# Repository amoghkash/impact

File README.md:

# impact
 impact concussion detection

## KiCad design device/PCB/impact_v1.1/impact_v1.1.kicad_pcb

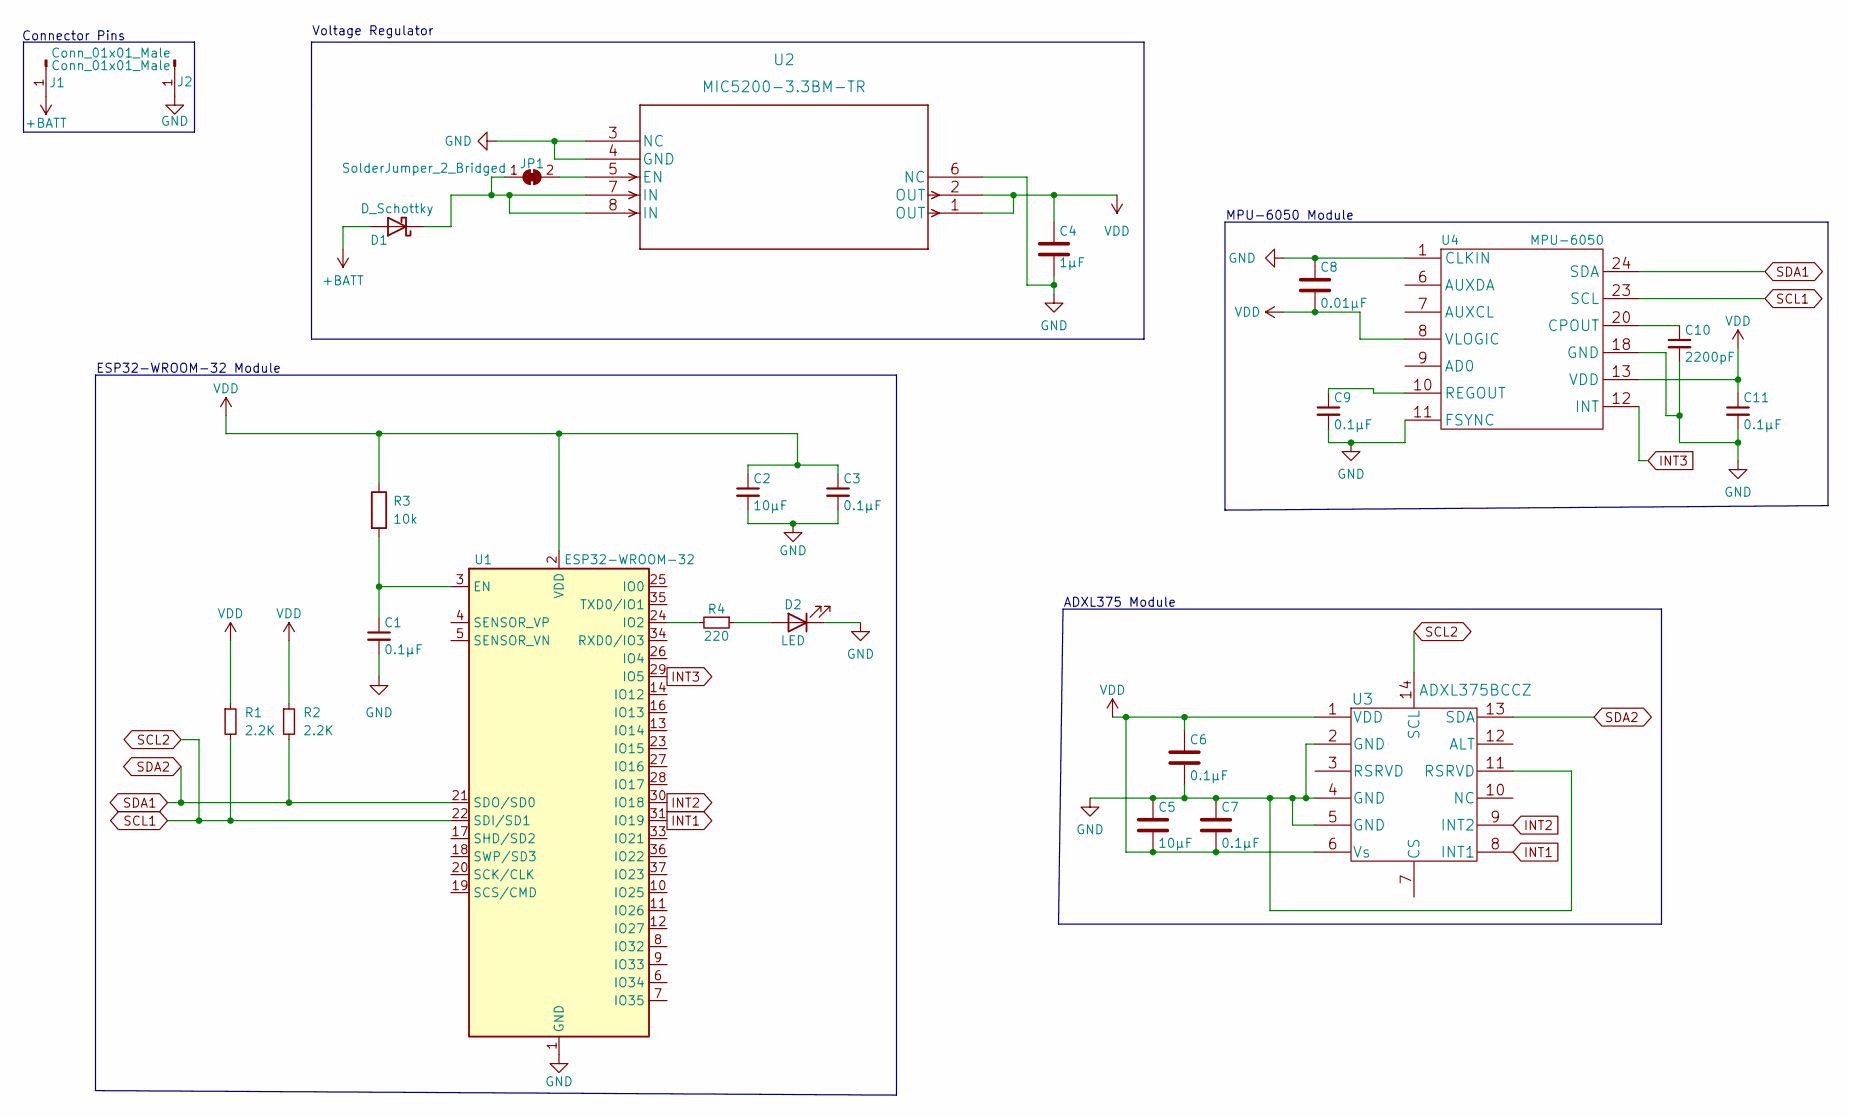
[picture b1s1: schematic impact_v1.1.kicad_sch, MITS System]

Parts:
C1, C3, C6, C7, C9, C11: 0.1µF; C_0201_0603Metric_Pad0.64x0.40mm_HandSolder
C2, C5: 10µF; C_0603_1608Metric_Pad1.08x0.95mm_HandSolder
C4: 1µF; C_0402_1005Metric_Pad0.74x0.62mm_HandSolder
C8: 0.01µF; C_0201_0603Metric_Pad0.64x0.40mm_HandSolder
C10: 2200pF; C_0402_1005Metric_Pad0.74x0.62mm_HandSolder
D1: D_Schottky; D_0402_1005Metric_Pad0.77x0.64mm_HandSolder
D2: LED; LED_0402_1005Metric_Pad0.77x0.64mm_HandSolder
J1: Conn_01x01_Male; TestPoint_Pad_3.0x3.0mm
J2: Conn_01x01_Male; TestPoint_Pad_D3.0mm
JP1: SolderJumper_2_Bridged; SolderJumper-2_P1.3mm_Bridged_Pad1.0x1.5mm
R1, R2: 2.2K; R_0201_0603Metric_Pad0.64x0.40mm_HandSolder
R3: 10k; R_0201_0603Metric_Pad0.64x0.40mm_HandSolder
R4: 220; R_0201_0603Metric_Pad0.64x0.40mm_HandSolder
U1: ESP32-WROOM-32
U2: MIC5200-3.3BM-TR; MIC5200-3.3YM
U3: ADXL375BCCZ
U4: MPU-6050; InvenSense_QFN-24_4x4mm_P0.5mm

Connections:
+BATT: D1.2 (A), J1.1; also elsewhere on the board
GND: C1.2, C2.2, C3.2, C4.2, C5.1, C6.2, C7.1, C8.1, C9.2, C10.2, C11.2, D2.1 (K), J2.1, U1.1 (GND), U1.15 (GND), U1.38 (GND), U1.39 (GND), U2.3 (NC), U2.4 (GND), U2.6 (NC), U3.2 (GND), U3.4 (GND), U3.5 (GND), U3.11 (RSRVD), U4.1 (CLKIN), U4.11 (FSYNC), U4.18 (GND); also elsewhere on the board
INT1: U1.31 (IO19), U3.8 (INT1)
INT2: U1.30 (IO18), U3.9 (INT2)
INT3: U1.29 (IO5), U4.12 (INT)
unnamed: C1.1, R3.2, U1.3 (EN)
unnamed: C9.1, U4.10 (REGOUT)
unnamed: C10.1, U4.20 (CPOUT)
unnamed: D1.1 (K), JP1.1 (A), U2.7 (IN), U2.8 (IN)
unnamed: D2.2 (A), R4.1
unnamed: JP1.2 (B), U2.5 (EN)
unnamed: R4.2, U1.24 (IO2)
SCL1: R1.2, U1.22 (SDI/SD1), U3.14 (SCL), U4.23 (SCL)
SDA1: R2.2, U1.21 (SDO/SD0), U3.13 (SDA), U4.24 (SDA)
VDD: C2.1, C3.1, C4.1, C5.2, C6.1, C7.2, C8.2, C11.1, R1.1, R2.1, R3.1, U1.2 (VDD), U2.1 (OUT), U2.2 (OUT), U3.1 (VDD), U3.6 (Vs), U4.8 (VLOGIC), U4.13 (VDD)

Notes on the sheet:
MPU-6050 Module
Connector Pins
ESP32-WROOM-32 Module
Voltage Regulator
ADXL375 Module

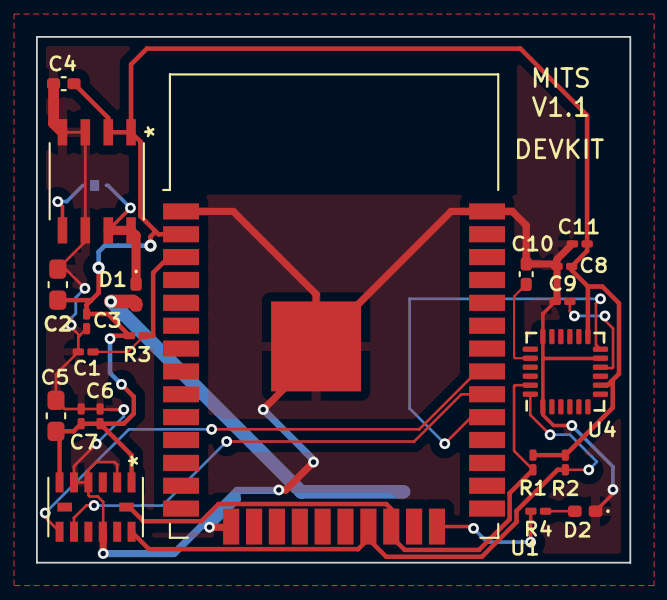
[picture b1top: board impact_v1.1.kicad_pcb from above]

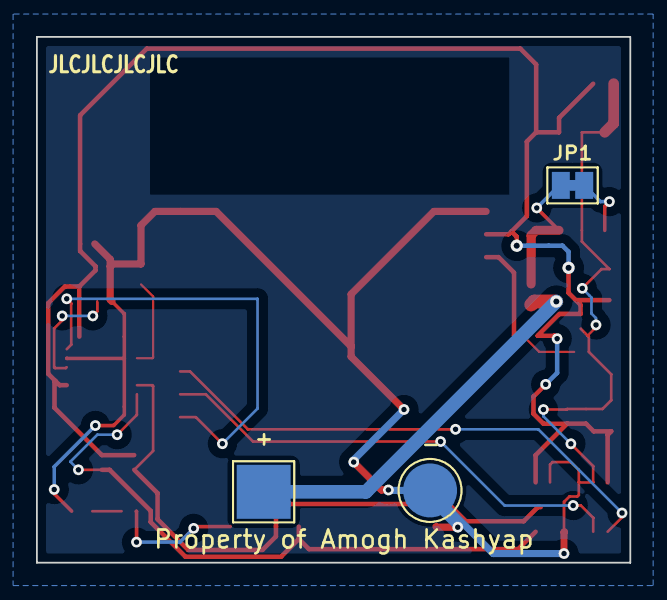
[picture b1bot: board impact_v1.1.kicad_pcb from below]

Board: 2 copper layers, 33.0 x 29.2 mm, 24 parts (3 on the bottom side), 15 nets.

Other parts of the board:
+: Conn_01x01_Male; TestPoint_Pad_3.0x3.0mm
-: Conn_01x01_Male; TestPoint_Pad_D3.0mm

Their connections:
+BATT: +.1; also elsewhere on the board
GND: -.1; also elsewhere on the board

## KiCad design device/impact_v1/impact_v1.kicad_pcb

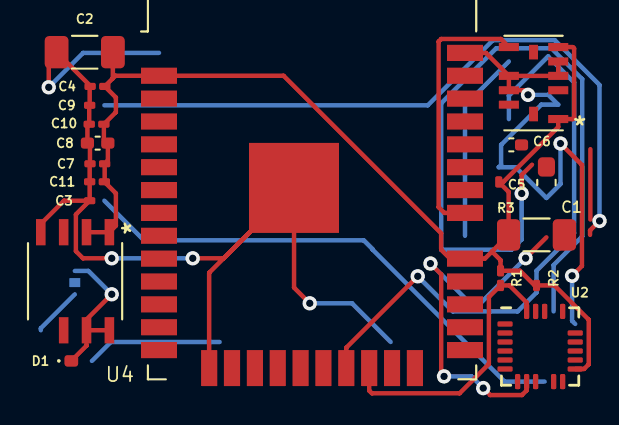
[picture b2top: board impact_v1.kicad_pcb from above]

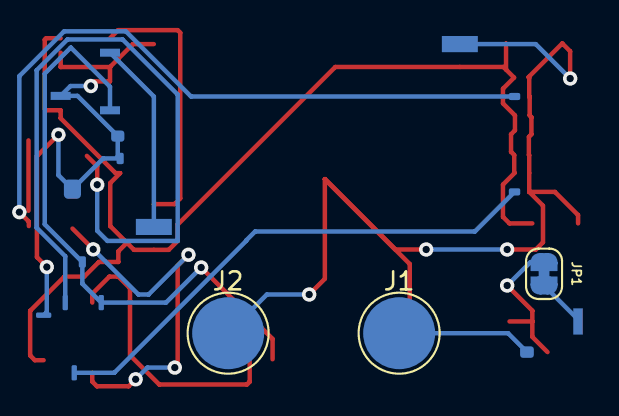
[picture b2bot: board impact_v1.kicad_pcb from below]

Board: 2 copper layers, 22 parts (3 on the bottom side), 14 nets.

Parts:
C1: 0.01µF; C_0603_1608Metric_Pad1.08x0.95mm_HandSolder
C2: 10µF; C_1206_3216Metric_Pad1.33x1.80mm_HandSolder
C3, C4, C5, C7, C9, C11: 0.1µF; C_0201_0603Metric_Pad0.64x0.40mm_HandSolder
C6: 2200pF; C_0402_1005Metric_Pad0.74x0.62mm_HandSolder
C8: 1µF; C_0402_1005Metric_Pad0.74x0.62mm_HandSolder
C10: 10µF; C_0201_0603Metric_Pad0.64x0.40mm_HandSolder
D1: D_Schottky; D_0402_1005Metric_Pad0.77x0.64mm_HandSolder
J1, J2: Conn_01x01_Male; TestPoint_Pad_D4.0mm
JP1: SolderJumper_2_Bridged; SolderJumper-2_P1.3mm_Bridged_RoundedPad1.0x1.5mm
R1, R2: 2.2K; R_0201_0603Metric_Pad0.64x0.40mm_HandSolder
R3: 10k; R_1206_3216Metric_Pad1.30x1.75mm_HandSolder
U1: MIC5200-3.3YM
U2: MPU-6050; InvenSense_QFN-24_4x4mm_P0.5mm
U3: ADXL375; ADXL375BCCZ
U4: ESP32-WROOM-32D; ESP32-WROOM-32

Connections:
+BATT: D1.2 (A), J1.1
GND: C1.2, C2.1, C3.2, C4.2, C5.1, C6.2, C7.2, C8.2, C9.2, C10.2, C11.2, J2.1, U1.4 (GND), U2.11 (FSYNC), U2.18 (GND), U3.2 (GND), U3.4 (GND), U3.5 (GND), U3.10 (NC), U3.11 (RSRVD), U4.1 (GND), U4.15 (GND), U4.38 (GND), U4.39 (GND)
unnamed: C1.1, U2.8 (VLOGIC)
unnamed: C3.1, U2.10 (REGOUT)
unnamed: C6.1, U2.20 (CPOUT)
unnamed: C9.1, R3.2, U4.3 (EN)
unnamed: D1.1 (K), JP1.1 (A), U1.7 (IN), U1.8 (IN)
unnamed: JP1.2 (B), U1.5 (EN)
unnamed: R1.2, U2.23 (SCL), U3.14 (SCL), U4.22 (SDI/SD1)
unnamed: R2.2, U2.24 (SDA), U3.13 (SDA), U4.21 (SDO/SD0)
unnamed: U3.8 (INT1), U4.31 (IO19)
unnamed: U3.9 (INT2), U4.30 (IO18)
unnamed: U2.12 (INT), U4.29 (IO5)
VDD: C2.2, C4.1, C5.2, C7.1, C8.1, C10.1, C11.1, R1.1, R2.1, R3.1, U1.1 (OUT), U1.2 (OUT), U2.13 (VDD), U3.1 (VDD), U3.6 (Vs), U4.2 (VDD)

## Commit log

2022-01-23 intiital
2022-01-23 initial
2022-01-23 Time Based Data Collection
2022-01-24 data collection
    improved user input and added waste-data + data filtering based on sample size
2022-01-24 Changed filestructure
2022-01-26 Added Hardware/PCB
    KiCad PCB and support files/folder added to repo
2022-01-26 Added Hardware PDFS and code improvements
    Improves a few aspects of code and added ML computation file in along with updates to hardware
2022-01-27 Updating KiCad Files
2022-01-28 Finished ADXL375
2022-01-28 Finished Schematics
2022-01-28 Added Footprints
2022-01-29 Routing
2022-01-30 Added Version 1.1
    Revamped version 1 to include better LED's and improved footprints
2022-01-30 End of Version 1
2022-01-30 LSV v1.1
2022-01-31 Production Version for v1.1
    Final Production version of v1.1. Sent to JLCPCB
2022-02-01 Added I2c Information
    for continuity over computers
2022-02-05 Pre Code Start
2022-02-18 Clean-Up
    File Reorganization and version 1.1 PCB completion
2022-02-22 Latest Working Version
    Added Local Scripts for Data collection and data collection embedded code.
2022-02-25 Latest Working Version
    - Real Time Data Logging from Device using UDP Server
    - Setup of StreamEngine for Machine Learning and data formatting
    - Ready for development of Machine Learning Software
2022-03-08 ML MODEL Complete
    Completed Designing and Coding Machine Learning Model to detect Impacts, currently at a 85.71% accuracy. Will be doing more testing and data collection in order to improve accuracy of results. Will b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
2022-03-08 Added Images for Proof in the Future
    New folder
2022-03-08 filled out .ipnyb file
2022-03-08 Basic .ipnyb file
2022-03-15 sdjfadjkshfsjkhasdf
    dfsbjjkfwhfkjewhje
2022-04-03 Before Computer Reset. Backu
2022-06-11 Final Commit Before Close
    Stable Version

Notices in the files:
parts and their libraries:
Copyright 2021 Accelerated Designs. All rights reserved.
